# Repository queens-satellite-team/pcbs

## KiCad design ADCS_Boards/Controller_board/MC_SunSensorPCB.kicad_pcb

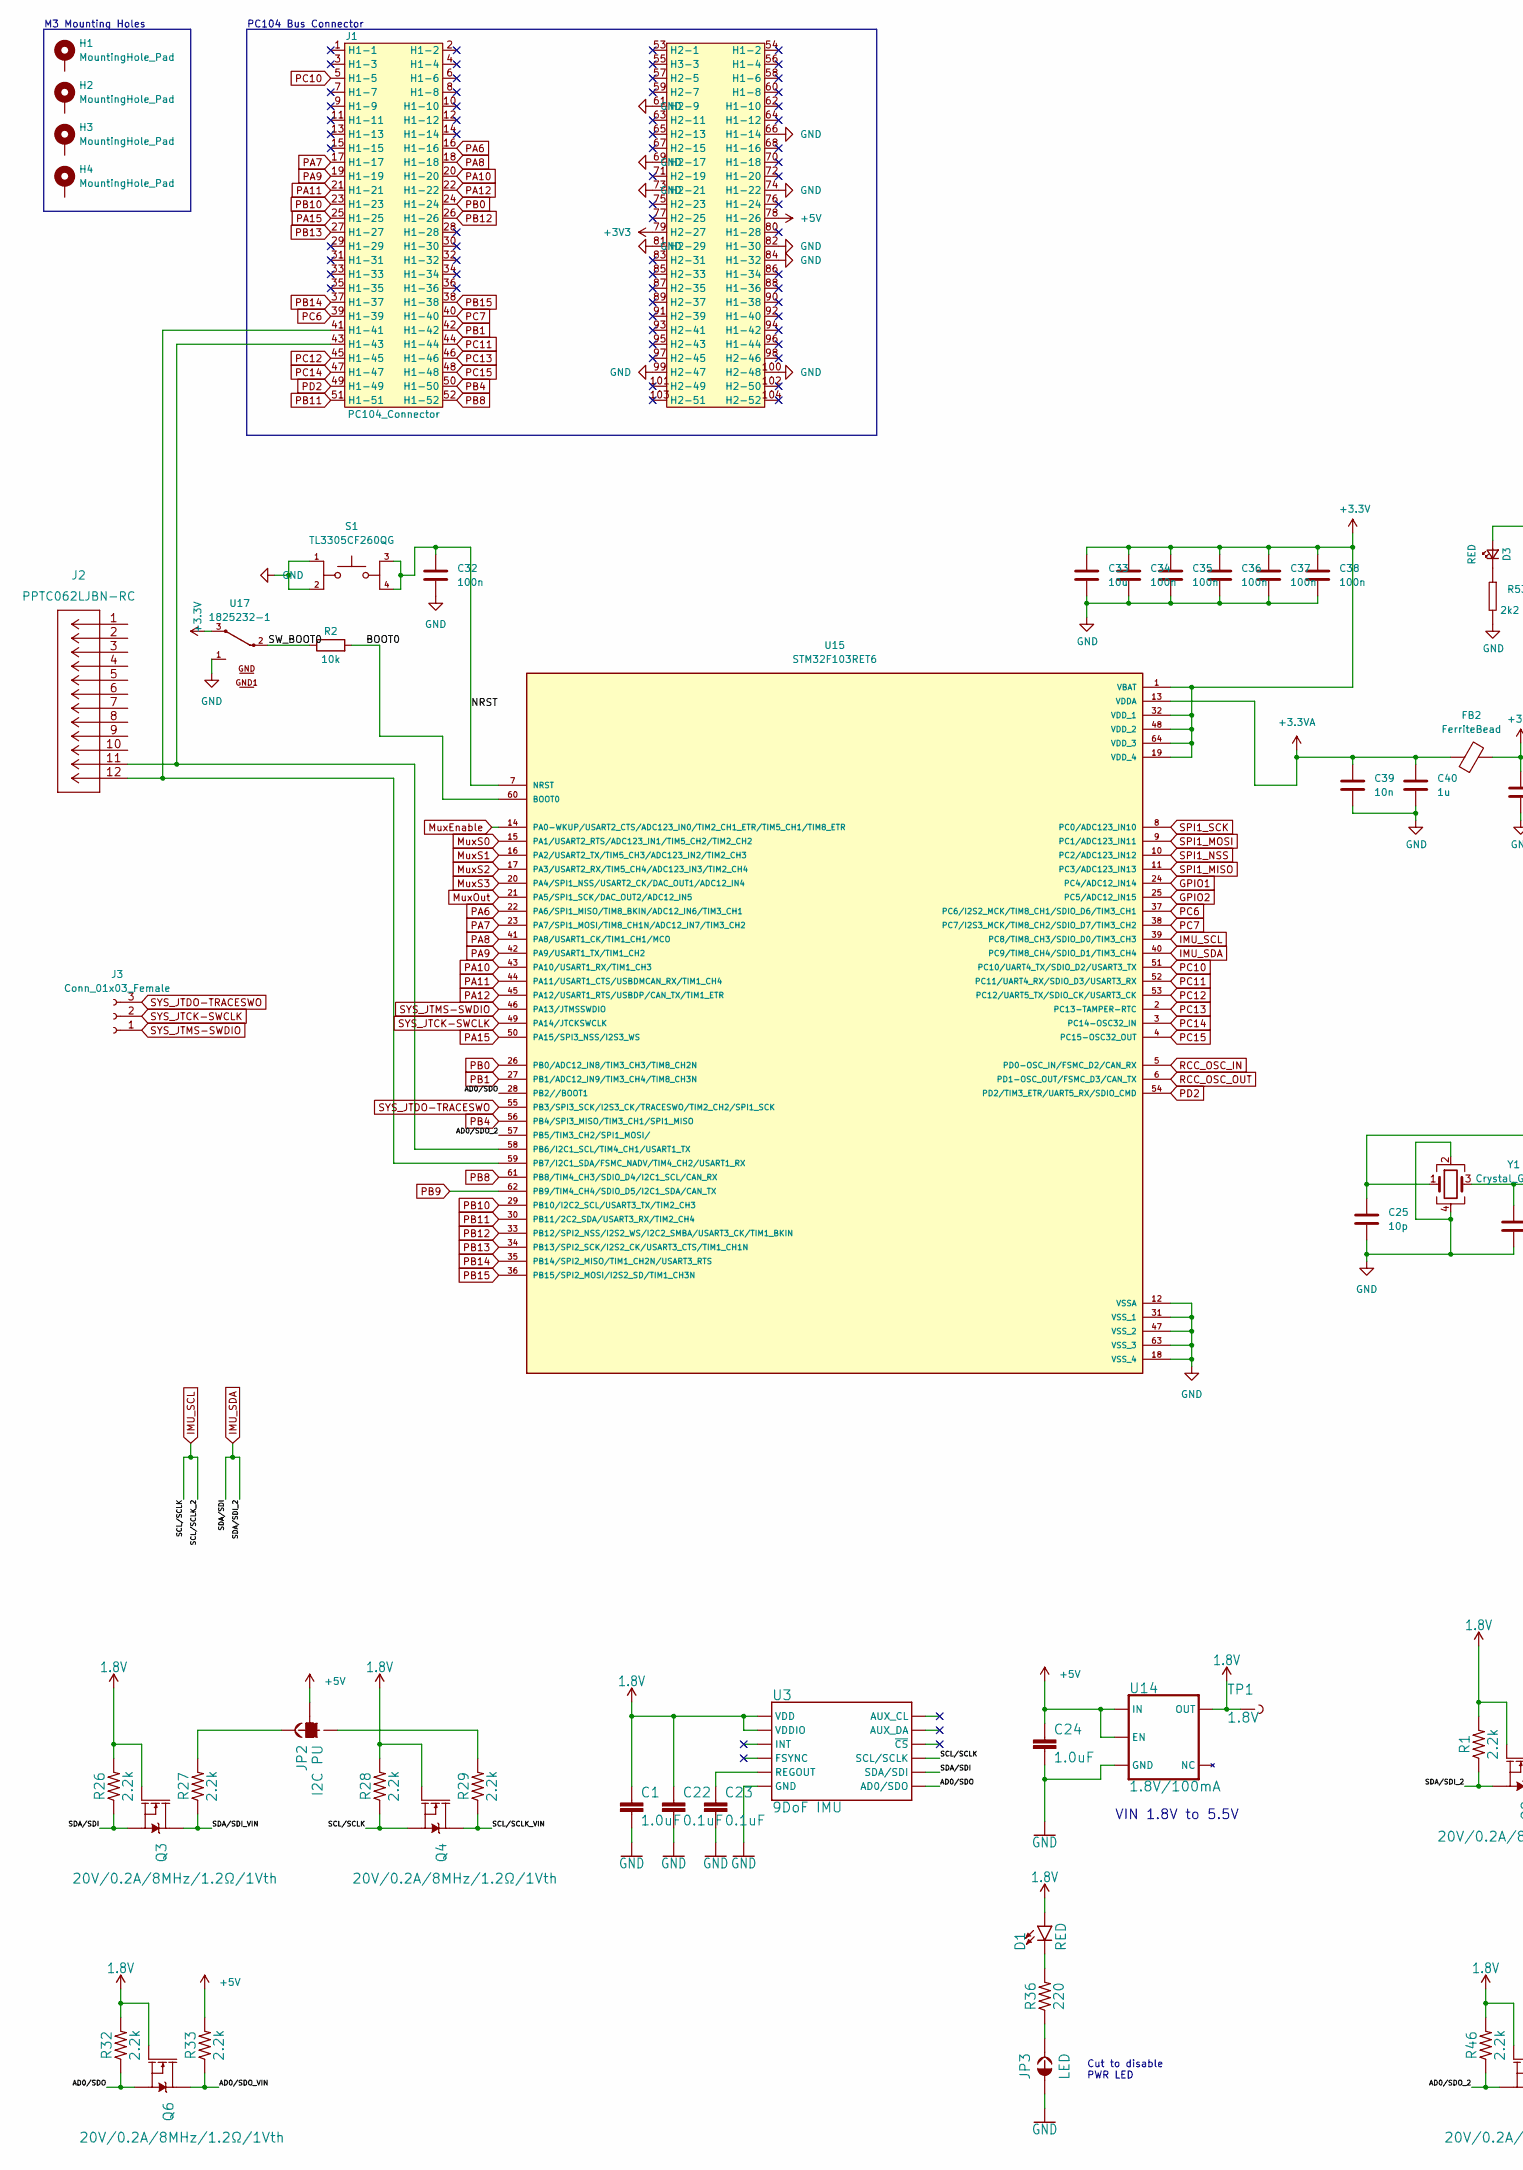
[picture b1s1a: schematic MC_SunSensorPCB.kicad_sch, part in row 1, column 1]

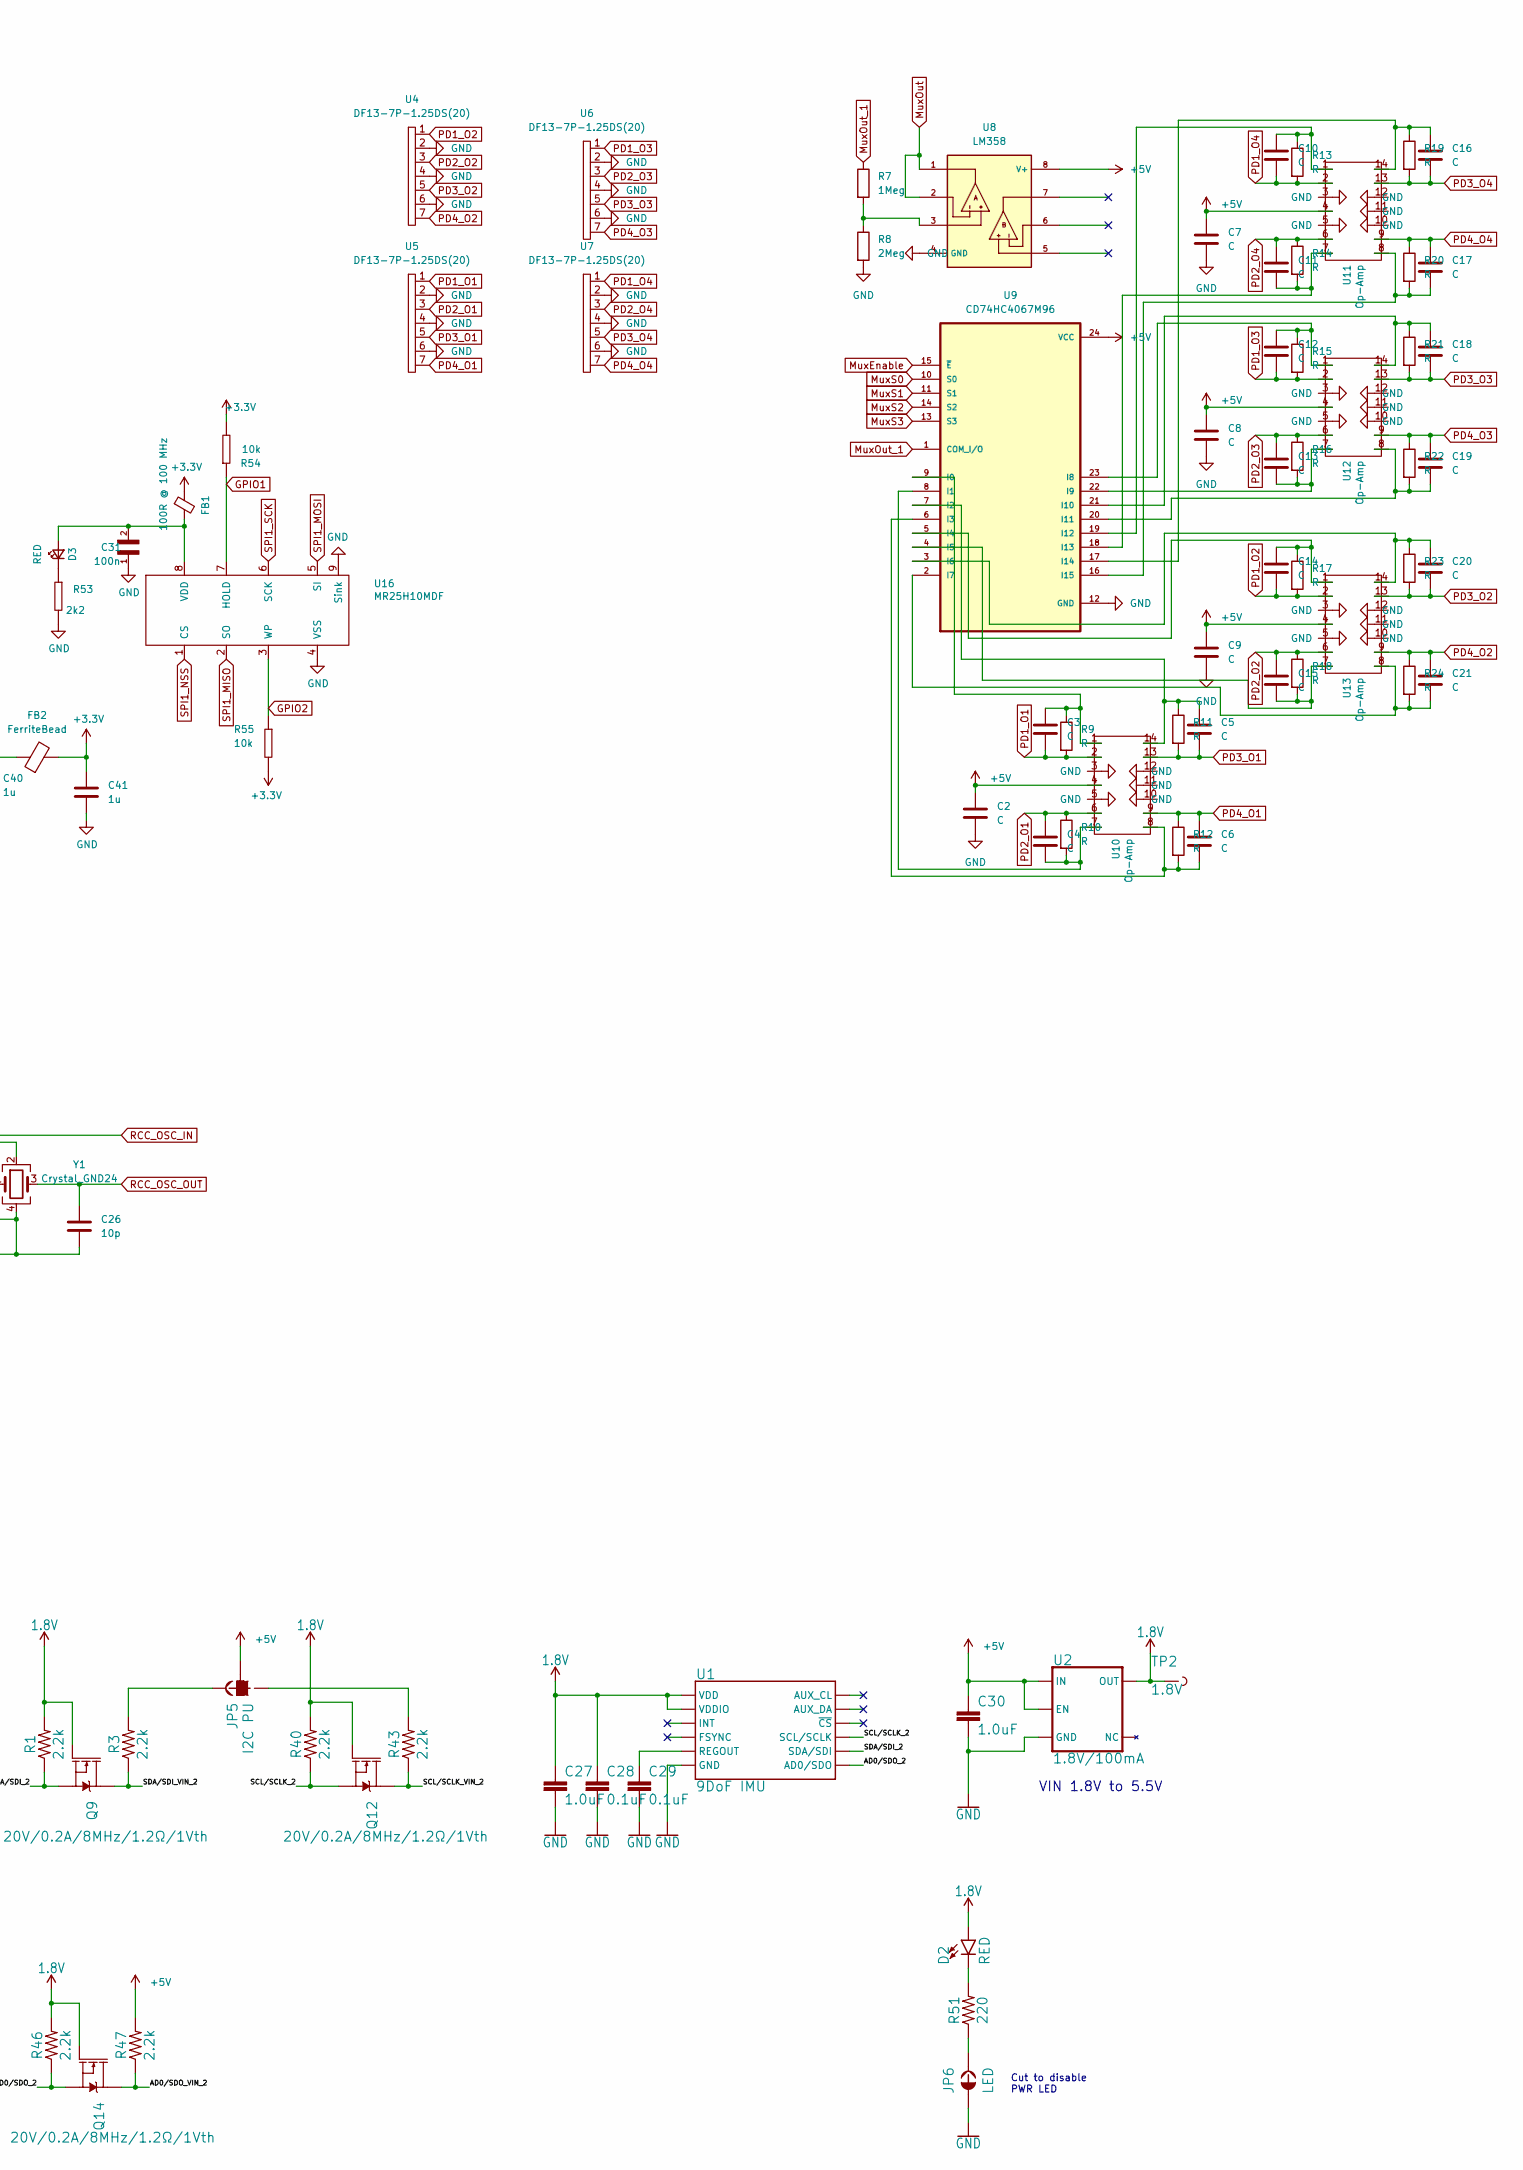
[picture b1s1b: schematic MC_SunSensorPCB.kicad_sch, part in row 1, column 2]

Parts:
C1, C24, C27, C30: 1.0uF; 0603
C2, C3, C4, C5, C6, C7, C8, C9, C10, C11, C12, C13, C14, C15, C16, C17, C18, C19, C20, C21: C; C_0603_1608Metric
C22, C23, C28, C29: 0.1uF; 0603
C25, C26: 10p; C_0603_1608Metric
C31: 100n; CAPC1608X90
C32, C34, C35, C36, C37, C38: 100n; C_0603_1608Metric
C33: 10u; C_0603_1608Metric
C39: 10n; C_0603_1608Metric
C40, C41: 1u; C_0603_1608Metric
D1, D2: RED; LED-0603
D3: RED; LED_0603_1608Metric_Pad1.05x0.95mm_HandSolder
FB1: 100R @ 100 MHz; INDUC1607X60N
FB2: FerriteBead; L_0603_1608Metric
H1, H2, H3, H4: MountingHole_Pad; MountingHole_3.2mm_M3_Pad_TopBottom
J1: PC104_Connector; pc104-connector
J2: PPTC062LJBN-RC
J3: Conn_01x03_Female; 1x3_Connector_Female
JP2, JP5: I2C PU; SMT-JUMPER_3_2-NC_TRACE_SILK
JP3, JP6: LED; SMT-JUMPER_2_NC_TRACE_SILK
Q3, Q4, Q6, Q9, Q12, Q14: 20V/0.2A/8MHz/1.2Ω/1Vth; SOT-416FL
R1, R3, R26, R27, R28, R29, R32, R33, R40, R43, R46, R47: 2.2k; 0402-TIGHT
R2: 10k; R_0603_1608Metric
R7: 1Meg; R_0603_1608Metric
R8: 2Meg; R_0603_1608Metric
R9, R10, R11, R12, R13, R14, R15, R16, R17, R18, R19, R20, R21, R22, R23, R24: R; R_0603_1608Metric
R36, R51: 220; 0603
R53: 2k2; RESC1607X60N
R54, R55: 10k; RESC1607X60N
S1: TL3305CF260QG; SW_TL3305CF260QG; PARTREV C
TP1, TP2: 1.8V; PAD.03X.03
U1, U3: 9DoF IMU; QFN24-3X3
U2, U14: 1.8V/100mA; SC70
U4, U5, U6, U7: DF13-7P-1.25DS(20); Hirose_DF13-07P-1.25DS_1x07_P1.25mm_Horizontal
U8: LM358; DIP794W45P254L959H508Q8
U9: CD74HC4067M96; SOIC127P1030X265-24N
U10, U11, U12, U13: Op-Amp
U15: STM32F103RET6; QFP50P1200X1200X160-64N
U16: MR25H10MDF; SON65P300X300X95-8N
U17: 1825232-1
Y1: Crystal_GND24; Crystal_SMD_3225-4Pin_3.2x2.5mm

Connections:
1.8V: C1.1, C22.1, C27.1, C28.1, D1.A, D2.A, Q3.1 (G), Q4.1 (G), Q6.1 (G), Q9.1 (G), Q12.1 (G), Q14.1 (G), R1.2, R26.2, R28.2, R32.2, R40.2, R46.2, TP1.P$1 (1), TP2.P$1 (1), U1.8 (VDDIO), U1.13 (VDD), U2.5 (OUT), U3.8 (VDDIO), U3.13 (VDD), U14.5 (OUT)
+3.3VA: C39.1, C40.1, FB2.1, U15.13 (VDDA)
+5V: C2.1, C7.1, C8.1, C9.1, C24.1, C30.1, J1.78 (H1-26), JP2.2, JP5.2, R33.2, R47.2, U2.1 (IN), U2.3 (EN), U8.8 (V+), U9.24 (VCC), U10.4, U11.4, U12.4, U13.4, U14.1 (IN), U14.3 (EN)
/AD0/SDO: Q6.2 (S), R32.1, U3.9 (AD0/SDO), U15.28 (PB2//BOOT1)
/AD0/SDO_2: Q14.2 (S), R46.1, U1.9 (AD0/SDO), U15.57 (PB5/TIM3_CH2/SPI1_MOSI/)
/AD0/SDO_VIN: Q6.3 (D), R33.1
/AD0/SDO_VIN_2: Q14.3 (D), R47.1
/BOOT0: R2.2, U15.60 (BOOT0)
/NRST: C32.1, S1.3, S1.4, U15.7 (NRST)
/SCL/SCLK_VIN: Q4.3 (D), R29.1
/SCL/SCLK_VIN_2: Q12.3 (D), R43.1
/SDA/SDI_VIN: Q3.3 (D), R27.1
/SDA/SDI_VIN_2: Q9.3 (D), R3.1
/SW_BOOT0: R2.1, U17.2
GND: C1.2, C2.2, C7.2, C8.2, C9.2, C22.2, C23.2, C24.2, C25.2, C26.2, C27.2, C28.2, C29.2, C30.2, C31.1, C32.2, C33.2, C34.2, C35.2, C36.2, C37.2, C38.2, C39.2, C40.2, C41.2, J1.61 (H2-9), J1.66 (H1-14), J1.69 (H2-17), J1.73 (H2-21), J1.74 (H1-22), J1.81 (H2-29), J1.82 (H1-30), J1.84 (H1-32), J1.99 (H2-47), J1.100 (H2-48), JP3.1, JP6.1, R8.2, R53.2, S1.1, S1.2, U1.18 (GND), U1.20 (GND), U2.2 (GND), U3.18 (GND), U3.20 (GND), U4.2, U4.4, U4.6, U5.2, U5.4, U5.6, U6.2, U6.4, U6.6, U7.2, U7.4, U7.6, U8.4 (GND), U9.12 (GND), U10.3, U10.5, U10.10, U10.11, U10.12, U11.3, U11.5, U11.10, U11.11, U11.12, U12.3, U12.5, U12.10, U12.11, U12.12, U13.3, U13.5, U13.10, U13.11, U13.12, U14.2 (GND), U15.12 (VSSA), U15.18 (VSS_4), U15.31 (VSS_1), U15.47 (VSS_2), U15.63 (VSS_3), U16.4 (VSS), U16.9 (Sink), U17.1, Y1.2, Y1.4
GPIO1: R54.1, U15.24 (PC4/ADC12_IN14), U16.7 (HOLD)
GPIO2: R55.1, U15.25 (PC5/ADC12_IN15), U16.3 (WP)
IMU_SCL: Q4.2 (S), Q12.2 (S), R28.1, R40.1, U1.23 (SCL/SCLK), U3.23 (SCL/SCLK), U15.39 (PC8/TIM8_CH3/SDIO_D0/TIM3_CH3)
IMU_SDA: Q3.2 (S), Q9.2 (S), R1.1, R26.1, U1.24 (SDA/SDI), U3.24 (SDA/SDI), U15.40 (PC9/TIM8_CH4/SDIO_D1/TIM3_CH4)
MuxEnable: U9.15 (~E), U15.14 (PA0-WKUP/USART2_CTS/ADC123_IN0/TIM2_CH1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)
MuxOut: U8.1, U8.2, U15.21 (PA5/SPI1_SCK/DAC_OUT2/ADC12_IN5)
MuxOut_1: R7.1, U9.1 (COM_I/O)
MuxS0: U9.10 (S0), U15.15 (PA1/USART2_RTS/ADC123_IN1/TIM5_CH2/TIM2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)
MuxS1: U9.11 (S1), U15.16 (PA2/USART2_TX/TIM5_CH3/ADC123_IN2/TIM2_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)
MuxS2: U9.14 (S2), U15.17 (PA3/USART2_RX/TIM5_CH4/ADC123_IN3/TIM2_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)
MuxS3: U9.13 (S3), U15.20 (PA4/SPI1_NSS/USART2_CK/DAC_OUT1/ADC12_I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)
unnamed: C3.1, R9.1, U9.9 (I0), U10.1
unnamed: C4.1, R10.2, U9.8 (I1), U10.7
unnamed: C5.1, R11.1, U9.7 (I2), U10.14
unnamed: C6.2, R12.2, U9.6 (I3), U10.8
unnamed: C10.1, R13.1, U9.19 (I12), U11.1
unnamed: C11.1, R14.2, U9.18 (I13), U11.7
unnamed: C12.1, R15.1, U9.23 (I8), U12.1
unnamed: C13.1, R16.2, U9.22 (I9), U12.7
unnamed: C14.1, R17.1, U9.5 (I4), U13.1
unnamed: C15.1, R18.2, U9.4 (I5), U13.7
unnamed: C16.1, R19.1, U9.17 (I14), U11.14
unnamed: C17.2, R20.2, U9.16 (I15), U11.8
unnamed: C18.1, R21.1, U9.21 (I10), U12.14
unnamed: C19.2, R22.2, U9.20 (I11), U12.8
unnamed: C20.1, R23.1, U9.3 (I6), U13.14
unnamed: C21.2, R24.2, U9.2 (I7), U13.8
unnamed: C23.1, U3.10 (REGOUT)
unnamed: C29.1, U1.10 (REGOUT)
unnamed: C31.2, D3.2 (A), FB1.2, U16.8 (VDD)
unnamed: D1.C, R36.2
unnamed: D2.C, R51.2
unnamed: D3.1 (K), R53.1
unnamed: J1.41 (H1-41), J2.12, U15.59 (PB7/I2C1_SDA/FSMC_NADV/TIM4_CH2/USART1_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)
unnamed: J1.43 (H1-43), J2.11, U15.58 (PB6/I2C1_SCL/TIM4_CH1/USART1_TX)
unnamed: JP2.1, R27.2
unnamed: JP2.3, R29.2
unnamed: JP3.2, R36.1
unnamed: JP5.1, R3.2
unnamed: JP5.3, R43.2
unnamed: JP6.2, R51.1
unnamed: R7.2, R8.1, U8.3
PA6: J1.16 (H1-16), U15.22 (PA6/SPI1_MISO/TIM8_BKIN/ADC12_IN6/TIM3_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)
PA7: J1.17 (H1-17), U15.23 (PA7/SPI1_MOSI/TIM8_CH1N/ADC12_IN7/TIM3_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)
PA8: J1.18 (H1-18), U15.41 (PA8/USART1_CK/TIM1_CH1/MCO)
PA9: J1.19 (H1-19), U15.42 (PA9/USART1_TX/TIM1_CH2)
PA10: J1.20 (H1-20), U15.43 (PA10/USART1_RX/TIM1_CH3)
PA11: J1.21 (H1-21), U15.44 (PA11/USART1_CTS/USBDMCAN_RX/TIM1_CH4)
PA12: J1.22 (H1-22), U15.45 (PA12/USART1_RTS/USBDP/CAN_TX/TIM1_ETR)
PA15: J1.25 (H1-25), U15.50 (PA15/SPI3_NSS/I2S3_WS)
PB0: J1.24 (H1-24), U15.26 (PB0/ADC12_IN8/TIM3_CH3/TIM8_CH2N)
PB1: J1.42 (H1-42), U15.27 (PB1/ADC12_IN9/TIM3_CH4/TIM8_CH3N)
PB4: J1.50 (H1-50), U15.56 (PB4/SPI3_MISO/TIM3_CH1/SPI1_MISO)
PB8: J1.52 (H1-52), U15.61 (PB8/TIM4_CH3/SDIO_D4/I2C1_SCL/CAN_RX)
PB9: U15.62 (PB9/TIM4_CH4/SDIO_D5/I2C1_SDA/CAN_TX)
PB10: J1.23 (H1-23), U15.29 (PB10/I2C2_SCL/USART3_TX/TIM2_CH3)
PB11: J1.51 (H1-51), U15.30 (PB11/2C2_SDA/USART3_RX/TIM2_CH4)
PB12: J1.26 (H1-26), U15.33 (PB12/SPI2_NSS/I2S2_WS/I2C2_SMBA/USART3_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)
PB13: J1.27 (H1-27), U15.34 (PB13/SPI2_SCK/I2S2_CK/USART3_CTS/TIM1_C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)
PB14: J1.37 (H1-37), U15.35 (PB14/SPI2_MISO/TIM1_CH2N/USART3_RTS)
PB15: J1.38 (H1-38), U15.36 (PB15/SPI2_MOSI/I2S2_SD/TIM1_CH3N)
PC6: J1.39 (H1-39), U15.37 (PC6/I2S2_MCK/TIM8_CH1/SDIO_D6/TIM3_CH1)
PC7: J1.40 (H1-40), U15.38 (PC7/I2S3_MCK/TIM8_CH2/SDIO_D7/TIM3_CH2)
PC10: J1.5 (H1-5), U15.51 (PC10/UART4_TX/SDIO_D2/USART3_TX)
PC11: J1.44 (H1-44), U15.52 (PC11/UART4_RX/SDIO_D3/USART3_RX)
PC12: J1.45 (H1-45), U15.53 (PC12/UART5_TX/SDIO_CK/USART3_CK)
PC13: J1.46 (H1-46), U15.2 (PC13-TAMPER-RTC)
PC14: J1.47 (H1-47), U15.3 (PC14-OSC32_IN)
PC15: J1.48 (H1-48), U15.4 (PC15-OSC32_OUT)
PD1_O1: C3.2, R9.2, U5.1, U10.2
PD1_O2: C14.2, R17.2, U4.1, U13.2
PD1_O3: C12.2, R15.2, U6.1, U12.2
PD1_O4: C10.2, R13.2, U7.1, U11.2
PD2: J1.49 (H1-49), U15.54 (PD2/TIM3_ETR/UART5_RX/SDIO_CMD)
PD2_O1: C4.2, R10.1, U5.3, U10.6
PD2_O2: C15.2, R18.1, U4.3, U13.6
PD2_O3: C13.2, R16.1, U6.3, U12.6
PD2_O4: C11.2, R14.1, U7.3, U11.6
PD3_O1: C5.2, R11.2, U5.5, U10.13
PD3_O2: C20.2, R23.2, U4.5, U13.13
PD3_O3: C18.2, R21.2, U6.5, U12.13
PD3_O4: C16.2, R19.2, U7.5, U11.13
PD4_O1: C6.1, R12.1, U5.7, U10.9
PD4_O2: C21.1, R24.1, U4.7, U13.9
PD4_O3: C19.1, R22.1, U6.7, U12.9
PD4_O4: C17.1, R20.1, U7.7, U11.9
RCC_OSC_IN: C25.1, U15.5 (PD0-OSC_IN/FSMC_D2/CAN_RX), Y1.1
RCC_OSC_OUT: C26.1, U15.6 (PD1-OSC_OUT/FSMC_D3/CAN_TX), Y1.3
SPI1_MISO: U15.11 (PC3/ADC123_IN13), U16.2 (SO)
SPI1_MOSI: U15.9 (PC1/ADC123_IN11), U16.5 (SI)
SPI1_NSS: U15.10 (PC2/ADC123_IN12), U16.1 (CS)
SPI1_SCK: U15.8 (PC0/ADC123_IN10), U16.6 (SCK)
SYS_JTCK-SWCLK: J3.2, U15.49 (PA14/JTCKSWCLK)
SYS_JTDO-TRACESWO: J3.3, U15.55 (PB3/SPI3_SCK/I2S3_CK/TRACESWO/TIM2_CH2/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)
SYS_JTMS-SWDIO: J3.1, U15.46 (PA13/JTMSSWDIO)

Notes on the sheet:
M3 Mounting Holes
VIN 1.8V to 5.5V
Cut to disable PWR LED
PC104 Bus Connector

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
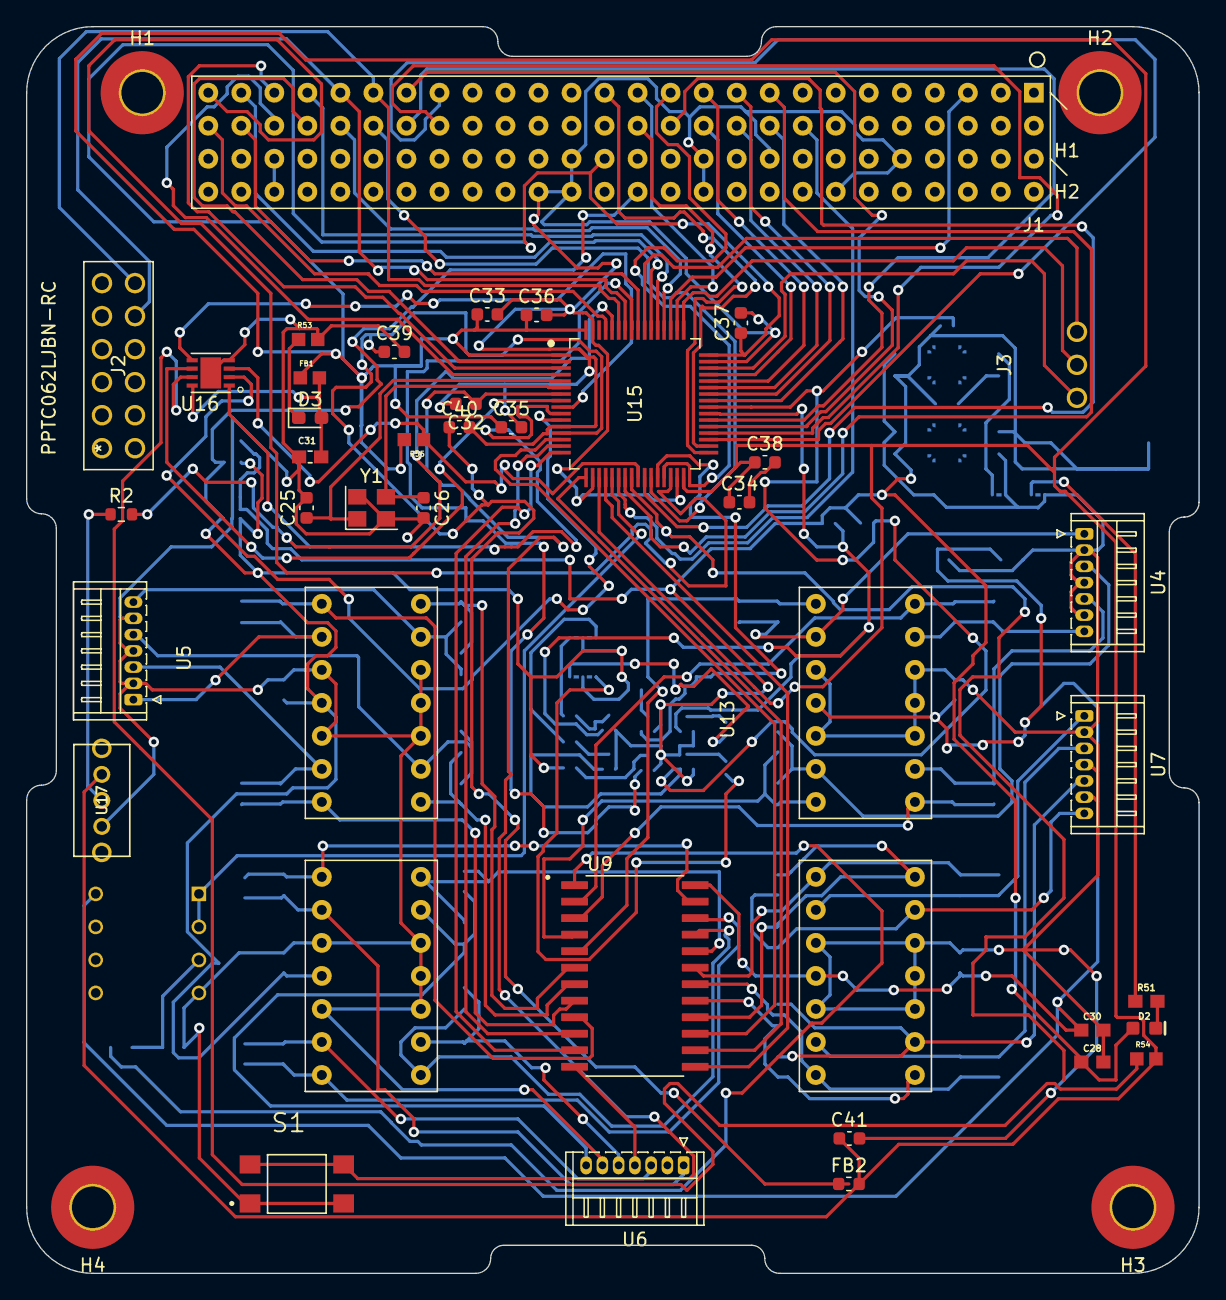
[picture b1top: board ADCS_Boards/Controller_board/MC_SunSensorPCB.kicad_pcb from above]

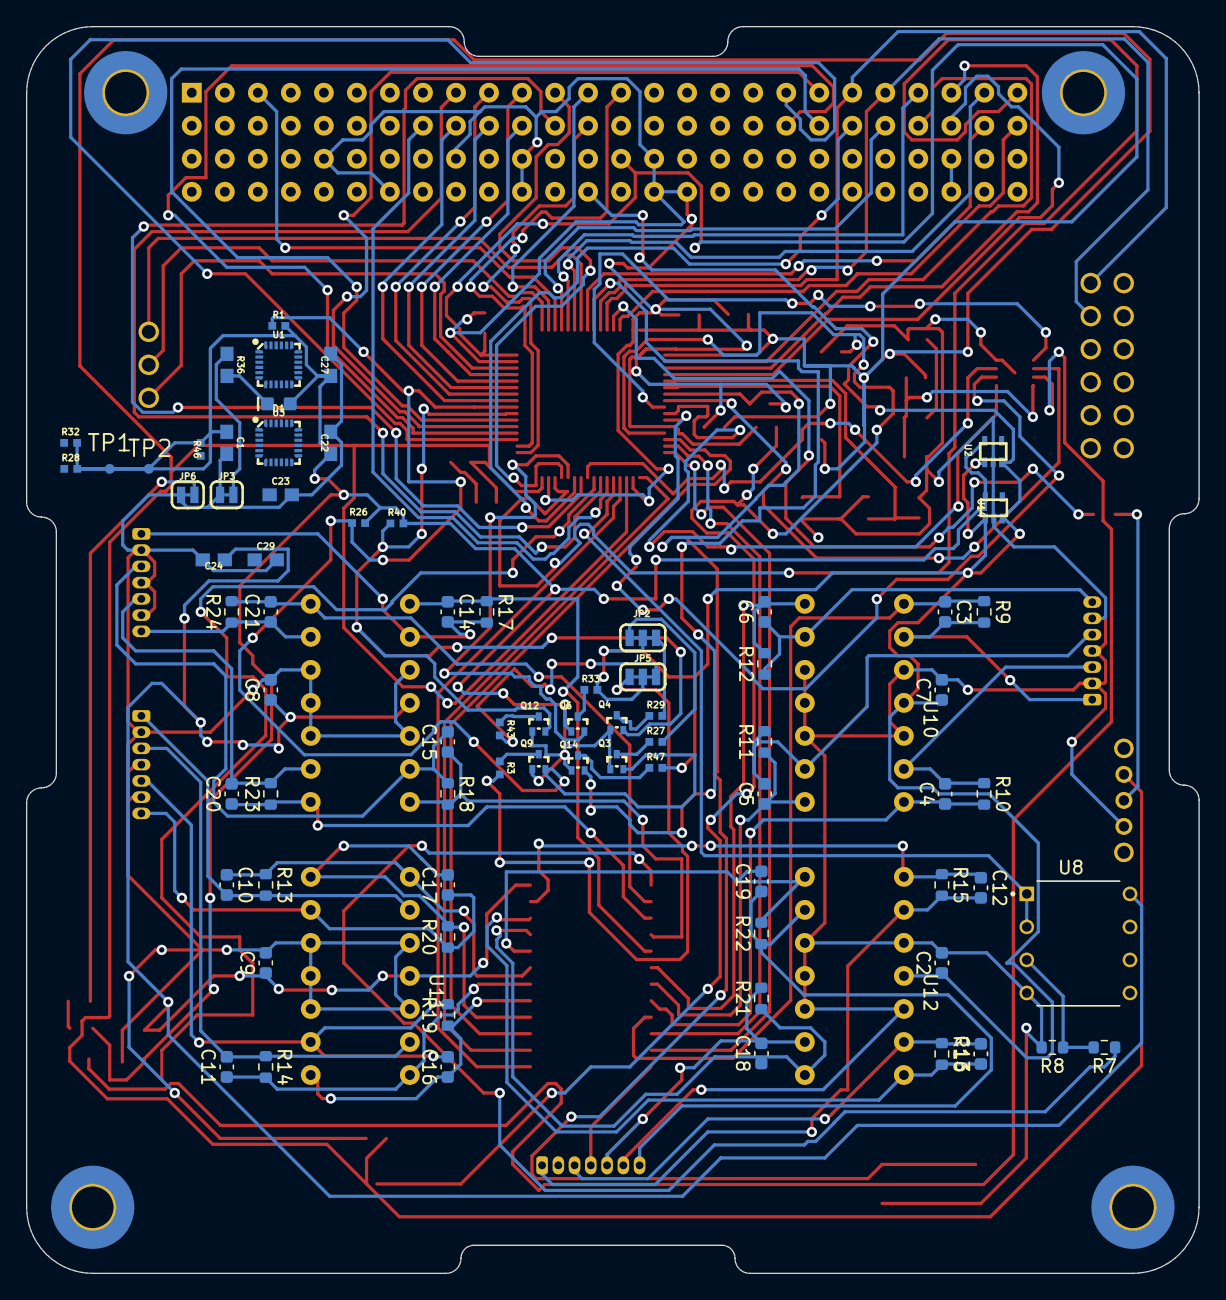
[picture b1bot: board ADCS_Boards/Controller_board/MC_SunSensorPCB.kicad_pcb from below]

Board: 4 copper layers, 90.2 x 95.9 mm, 120 parts (79 on the bottom side), 110 nets.

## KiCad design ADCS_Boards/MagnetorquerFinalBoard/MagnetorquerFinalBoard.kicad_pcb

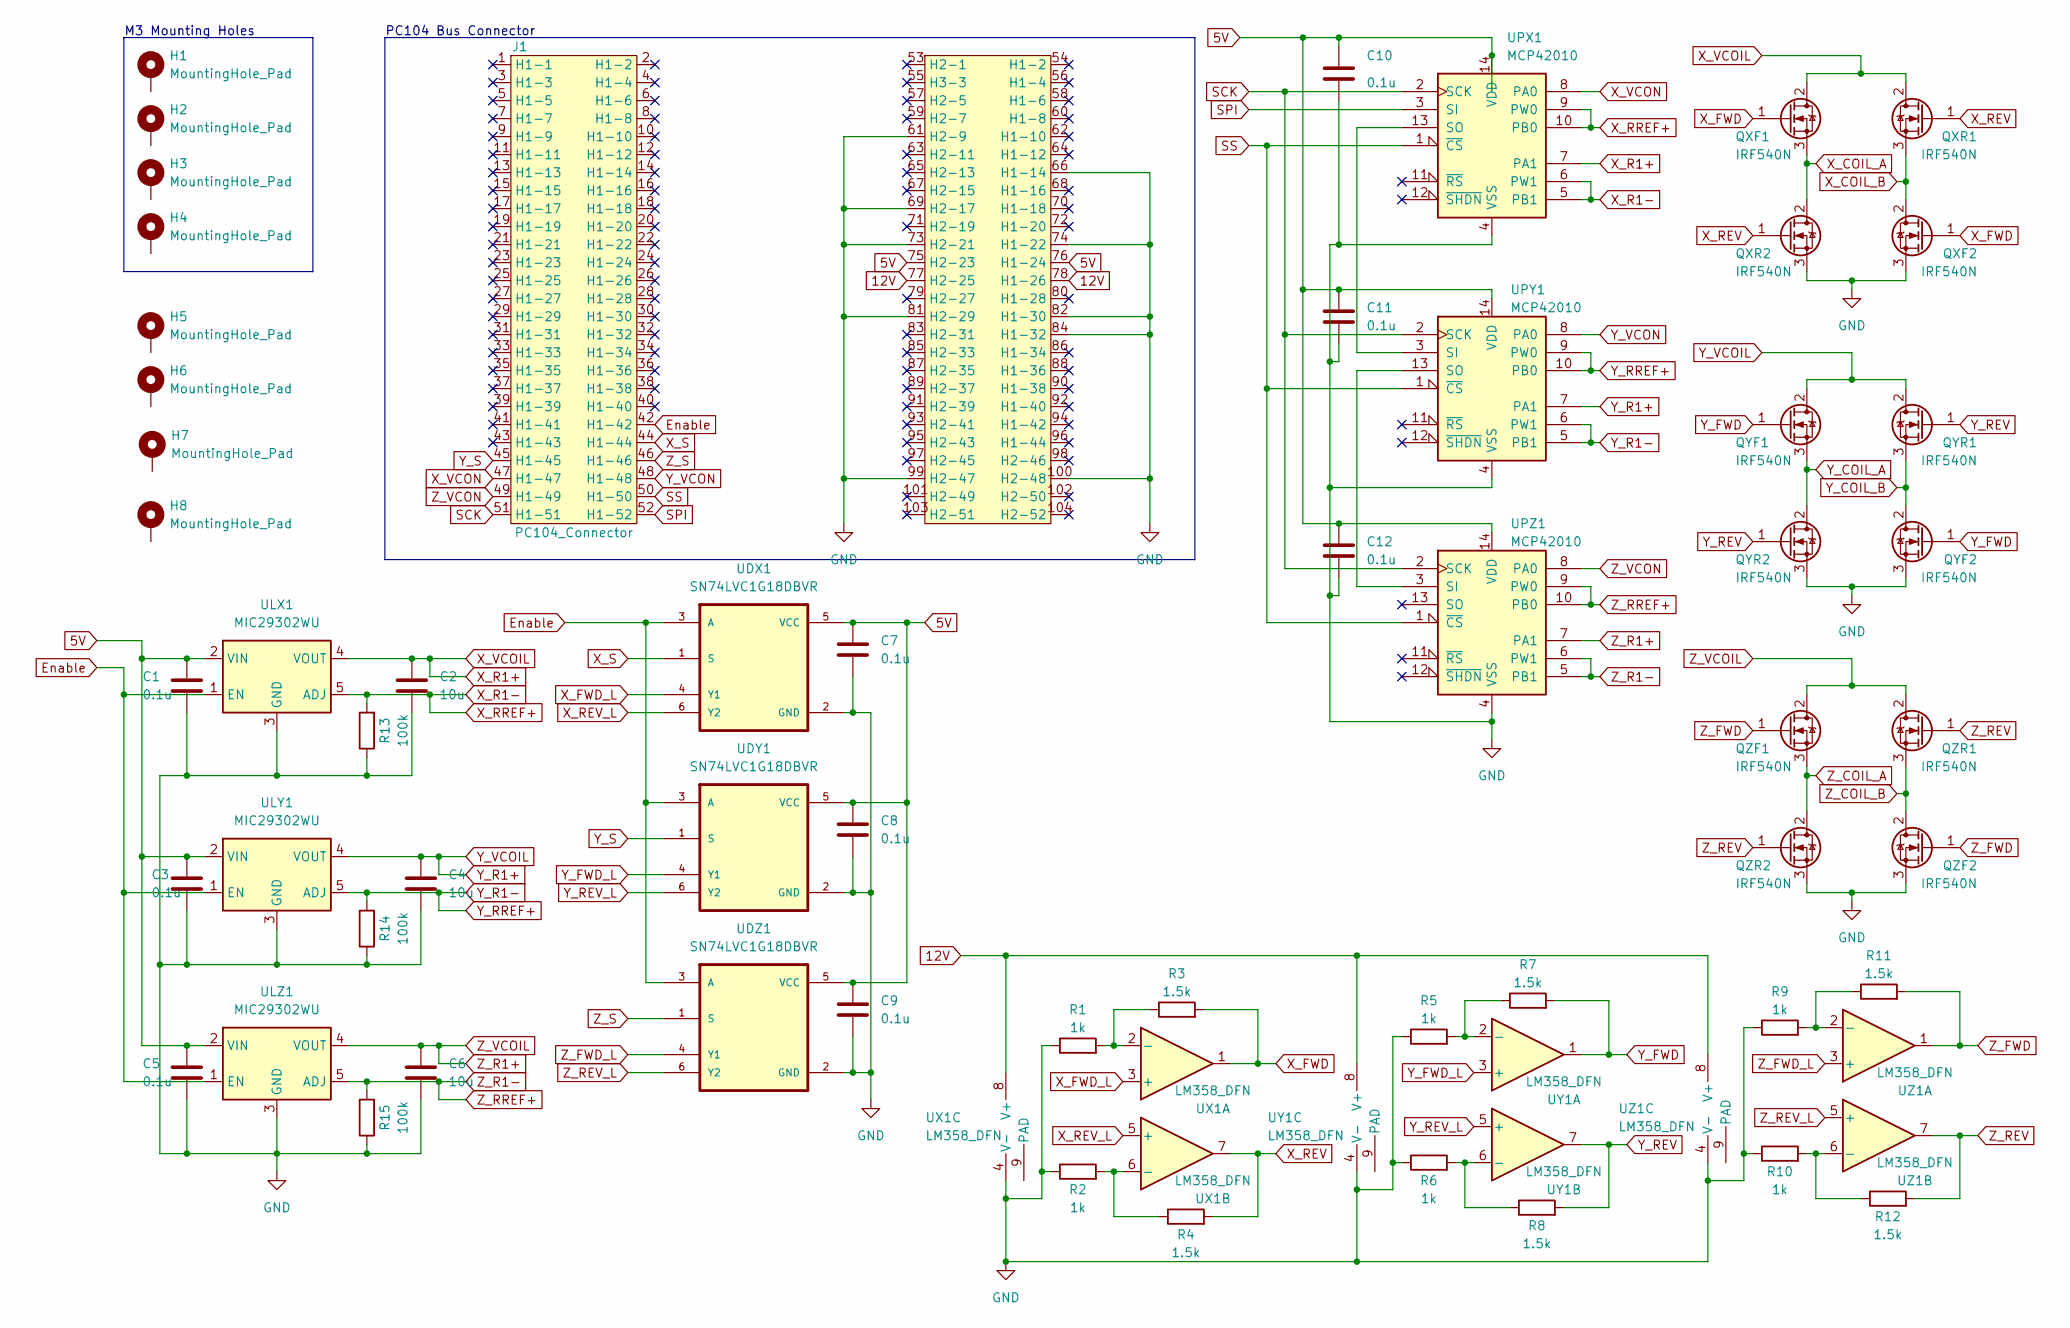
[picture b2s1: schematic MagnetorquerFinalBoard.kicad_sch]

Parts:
C1, C3, C5, C7, C8, C9, C10, C11, C12: 0.1u; C_0603_1608Metric
C2, C4, C6: 10u; C_0603_1608Metric
H1, H2, H3, H4: MountingHole_Pad; MountingHole_3.2mm_M3_Pad_TopBottom
H5, H6, H7, H8: MountingHole_Pad
J1: PC104_Connector; pc104-connector
QXF1, QXF2: IRF540N; TRANS_IRF540NSTRLPBF
QXR1, QXR2: IRF540N; TRANS_IRF540NSTRLPBF
QYF1, QYF2: IRF540N; TRANS_IRF540NSTRLPBF
QYR1, QYR2: IRF540N; TRANS_IRF540NSTRLPBF
QZF1, QZF2: IRF540N; TRANS_IRF540NSTRLPBF
QZR1, QZR2: IRF540N; TRANS_IRF540NSTRLPBF
R1, R2, R5, R6, R9, R10: 1k; R_0603_1608Metric
R3, R4, R7, R8, R11, R12: 1.5k; R_0603_1608Metric
R13, R14, R15: 100k; R_0603_1608Metric
UDX1: SN74LVC1G18DBVR; SOT95P280X145-6N
UDY1: SN74LVC1G18DBVR; SOT95P280X145-6N
UDZ1: SN74LVC1G18DBVR; SOT95P280X145-6N
ULX1: MIC29302WU; TO-263-5_TabPin3
ULY1: MIC29302WU; TO-263-5_TabPin3
ULZ1: MIC29302WU; TO-263-5_TabPin3
UPX1: MCP42010; SOIC127P600X175-14N
UPY1: MCP42010; SOIC127P600X175-14N
UPZ1: MCP42010; SOIC127P600X175-14N
UX1: LM358_DFN; DFN-8-1EP_2x2mm_P0.5mm_EP1.05x1.75mm
UY1: LM358_DFN; DFN-8-1EP_2x2mm_P0.5mm_EP1.05x1.75mm
UZ1: LM358_DFN; DFN-8-1EP_2x2mm_P0.5mm_EP1.05x1.75mm

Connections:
5V: C1.1, C3.1, C5.1, C7.1, C8.1, C9.1, C10.1, C11.1, C12.1, J1.75 (H2-23), J1.76 (H1-24), UDX1.5 (VCC), UDY1.5 (VCC), UDZ1.5 (VCC), ULX1.2 (VIN), ULY1.2 (VIN), ULZ1.2 (VIN), UPX1.14 (VDD), UPY1.14 (VDD), UPZ1.14 (VDD)
12V: J1.77 (H2-25), J1.78 (H1-26), UX1.8 (V+), UY1.8 (V+), UZ1.8 (V+)
Enable: J1.42 (H1-42), UDX1.3 (A), UDY1.3 (A), UDZ1.3 (A), ULX1.1 (EN), ULY1.1 (EN), ULZ1.1 (EN)
GND: C1.2, C2.2, C3.2, C4.2, C5.2, C6.2, C7.2, C8.2, C9.2, C10.2, C11.2, C12.2, J1.61 (H2-9), J1.66 (H1-14), J1.69 (H2-17), J1.73 (H2-21), J1.74 (H1-22), J1.81 (H2-29), J1.82 (H1-30), J1.84 (H1-32), J1.99 (H2-47), J1.100 (H2-48), QXF2.3 (S), QXR2.3 (S), QYF2.3 (S), QYR2.3 (S), QZF2.3 (S), QZR2.3 (S), R1.1, R2.1, R5.1, R6.1, R9.1, R10.1, R13.1, R14.1, R15.1, UDX1.2 (GND), UDY1.2 (GND), UDZ1.2 (GND), ULX1.3 (GND), ULY1.3 (GND), ULZ1.3 (GND), UPX1.4 (VSS), UPY1.4 (VSS), UPZ1.4 (VSS), UX1.4 (V-), UY1.4 (V-), UZ1.4 (V-)
unnamed: R1.2, R3.1, UX1.2 (-)
unnamed: R2.2, R4.1, UX1.6 (-)
unnamed: R5.2, R7.1, UY1.2 (-)
unnamed: R6.2, R8.1, UY1.6 (-)
unnamed: R10.2, R12.1, UZ1.6 (-)
unnamed: R9.2, R11.1, UZ1.2 (-)
unnamed: UPX1.13 (SO), UPY1.3 (SI)
unnamed: UPY1.13 (SO), UPZ1.3 (SI)
SCK: J1.51 (H1-51), UPX1.2 (SCK), UPY1.2 (SCK), UPZ1.2 (SCK)
SPI: J1.52 (H1-52), UPX1.3 (SI)
SS: J1.50 (H1-50), UPX1.1 (~CS), UPY1.1 (~CS), UPZ1.1 (~CS)
X_COIL_A: QXF1.3 (S), QXR2.2 (D)
X_COIL_B: QXF2.2 (D), QXR1.3 (S)
X_FWD: QXF1.1 (G), QXF2.1 (G), R3.2, UX1.1
X_FWD_L: UDX1.4 (Y1), UX1.3 (+)
X_R1+: C2.1, QXF1.2 (D), QXR1.2 (D), ULX1.4 (VOUT), UPX1.7 (PA1)
X_R1-: R13.2, ULX1.5 (ADJ), UPX1.5 (PB1), UPX1.6 (PW1), UPX1.9 (PW0), UPX1.10 (PB0)
X_REV: QXR1.1 (G), QXR2.1 (G), R4.2, UX1.7
X_REV_L: UDX1.6 (Y2), UX1.5 (+)
X_S: J1.44 (H1-44), UDX1.1 (S)
X_VCON: J1.47 (H1-47), UPX1.8 (PA0)
Y_COIL_A: QYF1.3 (S), QYR2.2 (D)
Y_COIL_B: QYF2.2 (D), QYR1.3 (S)
Y_FWD: QYF1.1 (G), QYF2.1 (G), R7.2, UY1.1
Y_FWD_L: UDY1.4 (Y1), UY1.3 (+)
Y_R1+: C4.1, QYF1.2 (D), QYR1.2 (D), ULY1.4 (VOUT), UPY1.7 (PA1)
Y_R1-: R14.2, ULY1.5 (ADJ), UPY1.5 (PB1), UPY1.6 (PW1), UPY1.9 (PW0), UPY1.10 (PB0)
Y_REV: QYR1.1 (G), QYR2.1 (G), R8.2, UY1.7
Y_REV_L: UDY1.6 (Y2), UY1.5 (+)
Y_S: J1.45 (H1-45), UDY1.1 (S)
Y_VCON: J1.48 (H1-48), UPY1.8 (PA0)
Z_COIL_A: QZF1.3 (S), QZR2.2 (D)
Z_COIL_B: QZF2.2 (D), QZR1.3 (S)
Z_FWD: QZF1.1 (G), QZF2.1 (G), R11.2, UZ1.1
Z_FWD_L: UDZ1.4 (Y1), UZ1.3 (+)
Z_R1+: C6.1, QZF1.2 (D), QZR1.2 (D), ULZ1.4 (VOUT), UPZ1.7 (PA1)
Z_R1-: R15.2, ULZ1.5 (ADJ), UPZ1.5 (PB1), UPZ1.6 (PW1), UPZ1.9 (PW0), UPZ1.10 (PB0)
Z_REV: QZR1.1 (G), QZR2.1 (G), R12.2, UZ1.7
Z_REV_L: UDZ1.6 (Y2), UZ1.5 (+)
Z_S: J1.46 (H1-46), UDZ1.1 (S)
Z_VCON: J1.49 (H1-49), UPZ1.8 (PA0)

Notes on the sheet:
M3 Mounting Holes
PC104 Bus Connector
